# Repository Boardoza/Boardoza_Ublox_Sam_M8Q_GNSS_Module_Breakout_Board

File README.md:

# UBLOX SAM M8Q GNSS Module Breakout Board

The **Boardoza SAM-M8Q GNSS Breakout Module** is a **high-performance multi-GNSS receiver** designed for **precise positioning applications**. It integrates the **u-blox SAM-M8Q module**, which supports **GPS, GLONASS, and Galileo** satellite constellations for improved accuracy and reliability.  

This module operates with **3.3V or 5V**, making it compatible with a wide range of microcontrollers. It communicates with an MCU via **I<sup>2</sup>C and UART** interfaces, providing flexible integration for various applications, including **navigation systems, asset tracking, drones, and IoT-based geolocation solutions**.  

The **PPS, RST, INT, and SAFE** pins operate at **3.3V**, ensuring seamless interfacing with low-power microcontrollers.  

## [Click here to purchase!](https://www.ozdisan.com/maker-ve-iot-urunleri/boardoza/boardoza-modulleri/BOARDOZA-UBLOX/1206512)

|Front Side|Back Side|
|:---:|:---:|
| | |

---

## Key Features

- **Multi-GNSS Support:** Compatible with GPS, GLONASS, and Galileo for enhanced positioning accuracy.  
- **Flexible Power Compatibility:** Operates with **3.3V or 5V**, making it suitable for a variety of MCUs.  
- **Dual Communication Interfaces:** Supports both **I<sup>2</sup>C and UART** for versatile connectivity.  
- **Time Pulse Output (PPS):** Provides precise timing synchronization at **1 pulse per second (default)**.  
- **Low Power Consumption:** Ideal for battery-operated applications such as **wearables and IoT tracking devices**.  
- **Industrial-Grade Performance:** Works reliably in extreme environments with a **temperature range of -40°C to +85°C**.  
- **Future-Proof Design:** Includes a **SAFEBOOT_N** function pin for firmware updates and configuration changes.  

---

## Technical Specifications

**Model:** u-blox SAM-M8Q  
**Input Voltage:** 3.3V - 5.5V  
**Voltage Input Type:** 4-pin 2.50mm header  
**Functions:** I<sup>2</sup>C and UART GNSS Receiver  
**Satellite Support:** GPS, GLONASS, Galileo, BeiDou  
**Time Pulse (PPS) Accuracy:** ±30 ns (typical)  
**Operating Temperature:** -40°C to +85°C  
**Board Dimensions:** 40mm x 40mm  

---

## Board Pinout

### **( J1 ) UART Communication Pins**  

| Pin Number | Pin Name | Description |
|:---:|:---:|---|
| 1 | GND | Ground |
| 2 | TXD | Transmitted Data Pin |
| 3 | RXD | Received Data Pin |
| 4 | VCC | Power Supply (3.3V - 5.5V) |

### **( J2 ) I<sup>2</sup>C Communication Pins**  

| Pin Number | Pin Name | Description |
|:---:|:---:|---|
| 1 | GND | Ground |
| 2 | SDA | I<sup>2</sup>C Serial Data Pin |
| 3 | SCL | I<sup>2</sup>C Serial Clock Pin |
| 4 | VCC | Power Supply (3.3V - 5.5V) |

### **( J3 ) Additional Function Pins**  

| Pin Number | Pin Name | Description |
|:---:|:---:|---|
| 1 | PPS | Time pulse signal (default: 1 pulse per second). See the u-blox M8 protocol specification for details. |
| 2 | RST | Active LOW reset pin. Internally pulled up to VCC. |
| 3 | INT | Used for time or frequency aiding data input to the receiver. |
| 4 | SAFE | SAFEBOOT_N function pin for firmware updates and reconfiguration (Reserved). |

---

## Board Dimensions

---

## Step Files

[Boardoza UBLOX SAM M8Q.step](./assets/UBLOX_SAM_M8Q%20Step.step)

---

## Datasheet

[Boardoza UBLOX SAM M8Q Datasheet.pdf](./assets/UBLOX_SAM_M8Q%20Datasheet.pdf)

---

## Version History

- V1.0.0 - Initial Release

---

## Support

- If you have any questions or need support, please contact <support@boardoza.com>

---

## License

Shield: [![CC BY-SA 4.0][cc-by-sa-shield]][cc-by-sa]

This work is licensed under a [Creative Commons Attribution-ShareAlike 4.0 International License][cc-by-sa].

[![CC BY-SA 4.0][cc-by-sa-image]][cc-by-sa]

[cc-by-sa]: http://creativecommons.org/licenses/by-sa/4.0/
[cc-by-sa-image]: https://licensebuttons.net/l/by-sa/4.0/88x31.png
[cc-by-sa-shield]: https://img.shields.io/badge/License-CC%20BY--SA%204.0-lightgrey.svg

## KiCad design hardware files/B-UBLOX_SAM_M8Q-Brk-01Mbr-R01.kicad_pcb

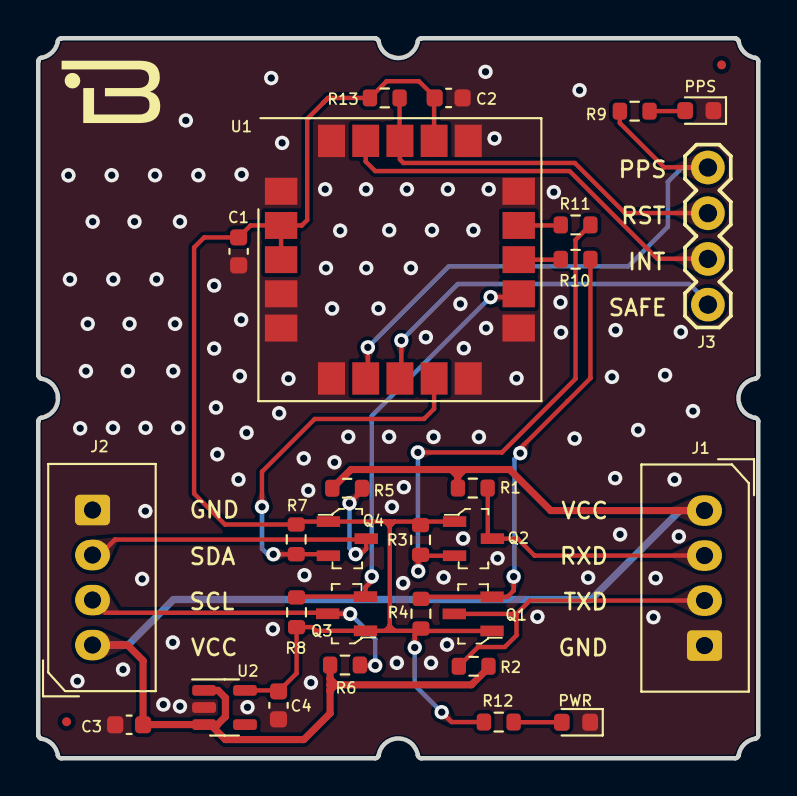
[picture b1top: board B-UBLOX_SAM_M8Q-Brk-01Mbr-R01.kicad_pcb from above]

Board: 2 copper layers, 40.0 x 40.0 mm, 28 parts (0 on the bottom side), 19 nets.

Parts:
C1, C2: 100nF; C_0603_1608Metric
C3, C4: 1uF; C_0603_1608Metric
J1, J2: MOLEX_CONNECTOR_1X4; 2317-04S_1x04_P2.50mm_Vertical
J3: CONN_04; 1X04
PPS: LED RED; LED_0603_1608Metric
PWR: LED POWER; LED_0603_1608Metric
Q1, Q2, Q3, Q4: 2N7002_R1_00001; SOT-23-3
R1, R2, R3, R4, R5, R6, R7, R8, R9, R12, R13: 10K; R_0603_1608Metric
R10, R11: 470; R_0603_1608Metric
U1: ublox_SAM-M8Q
U2: TLV73333PDBVR; SOT-23-5

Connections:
+3V3: C1.1, C2.1, C4.1, Q1.1 (G), Q2.1 (G), Q3.1 (G), Q4.1 (G), R3.1, R4.1, R7.1, R8.1, R12.1, R13.2, U1.2 (VCC_IO), U1.3 (V_BCKP), U1.17 (VCC), U2.5 (OUT)
GND: C1.2, C2.2, C3.2, C4.2, J1.4, J2.4, PPS.1 (K), PWR.1 (K), U1.1 (GND), U1.4 (GND), U1.5 (GND), U1.6 (GND), U1.10 (GND), U1.11 (GND), U1.15 (GND), U1.16 (GND), U1.20 (GND), U2.2 (GND)
GPS_INT: J3.3, U1.19 (EXTINT)
GPS_RX: R11.2, U1.14 (RXD)
GPS_SCL: Q3.2 (S), R8.2, U1.12 (SCL)
GPS_SDA: Q4.2 (S), R7.2, U1.9 (SDA)
GPS_TX: R10.2, U1.13 (TXD)
unnamed: PPS.2 (A), R9.2
unnamed: PWR.2 (A), R12.2
unnamed: Q1.2 (S), R4.2, R10.1
unnamed: Q2.2 (S), R3.2, R11.1
PPS: J3.1, R9.1, U1.7 (TIMEPULSE)
RESET: J3.2, R13.1, U1.18 (~RESET)
RXD: J1.2, Q2.3 (D), R1.2
SAFEBOOT: J3.4, U1.8 (~SAFEBOOT)
SCL: J2.2, Q3.3 (D), R6.2
SDA: J2.3, Q4.3 (D), R5.2
TXD: J1.3, Q1.3 (D), R2.2
VCC: C3.1, J1.1, J2.1, R1.1, R2.1, R5.1, R6.1, U2.1 (IN), U2.3 (EN)
